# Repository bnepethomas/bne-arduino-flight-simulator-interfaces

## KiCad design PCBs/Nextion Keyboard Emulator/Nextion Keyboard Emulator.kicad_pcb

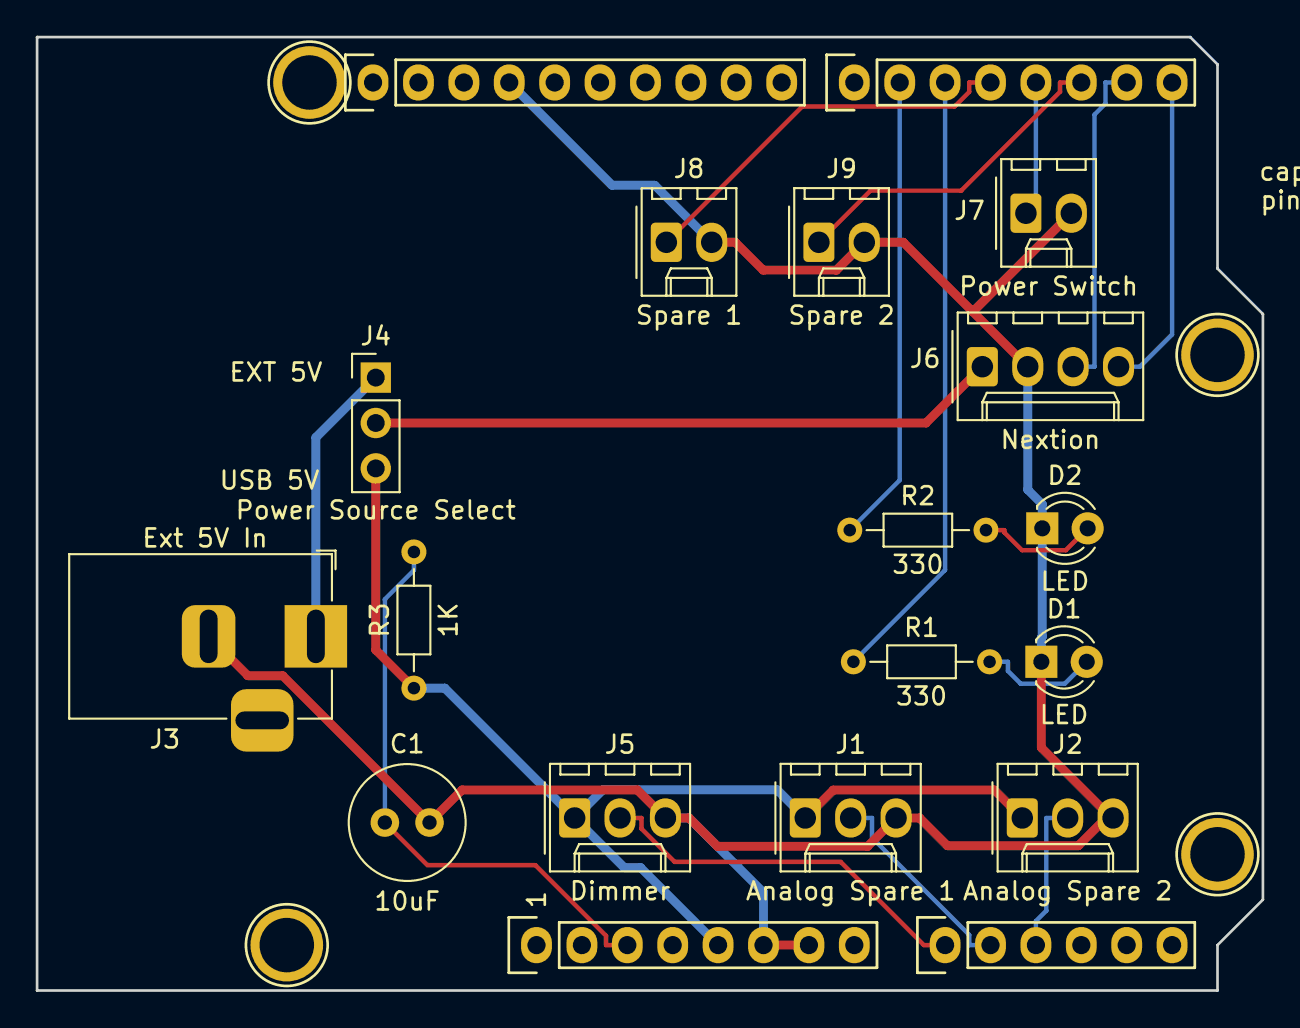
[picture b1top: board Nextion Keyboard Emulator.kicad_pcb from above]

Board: 2 copper layers, 68.6 x 53.3 mm, 23 parts (0 on the bottom side), 17 nets.

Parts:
C1: 10uF; C_Radial_D6.3mm_H5.0mm_P2.50mm
D1, D2: LED; LED_D3.0mm
J1: Analog Spare 1; Molex_KK-254_AE-6410-03A_1x03_P2.54mm_Vertical
J2: Analog Spare 2; Molex_KK-254_AE-6410-03A_1x03_P2.54mm_Vertical
J3: Ext 5V In; BarrelJack_Horizontal
J4: Power Source Select; PinHeader_1x03_P2.54mm_Vertical
J5: Dimmer; Molex_KK-254_AE-6410-03A_1x03_P2.54mm_Vertical
J6: Nextion; Molex_KK-254_AE-6410-04A_1x04_P2.54mm_Vertical
J7: Power Switch; Molex_KK-254_AE-6410-02A_1x02_P2.54mm_Vertical
J8: Spare 1; Molex_KK-254_AE-6410-02A_1x02_P2.54mm_Vertical
J9: Spare 2; Molex_KK-254_AE-6410-02A_1x02_P2.54mm_Vertical
P1: Power; Socket_Strip_Arduino_1x08
P2: Analog; Socket_Strip_Arduino_1x06
P3: Digital; Socket_Strip_Arduino_1x10
P4: Digital; Socket_Strip_Arduino_1x08
P5, P6, P7, P8: CONN_01X01; Arduino_1pin
R1, R2: 330; R_Axial_DIN0204_L3.6mm_D1.6mm_P7.62mm_Horizontal
R3: 1K; R_Axial_DIN0204_L3.6mm_D1.6mm_P7.62mm_Horizontal

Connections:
+5V: J1.1, J2.1, J4.3, J5.1, P1.5, R3.1
+5VD: J4.2, J6.1
/0(Rx): J6.4, P4.8
/1(Tx): J6.3, P4.7
/2: J9.1, P4.6
/3(**): J7.1, P4.5
/4: J8.1, P4.4
/5(**): P4.3, R1.1
/6(**): P4.2, R2.1
/A0: J5.2, P2.1
/A1: J1.2, P2.2
/A2: J2.2, P2.3
/EXT5VIN: J3.1, J4.1
/Reset: C1.1, P1.3, R3.2
GND: C1.2, D1.1, D2.1, J1.3, J2.3, J3.2, J5.3, J6.2, J7.2, J8.2, J9.2, P1.6, P1.7, P3.4
unnamed: D1.2, R1.2
unnamed: D2.2, R2.2

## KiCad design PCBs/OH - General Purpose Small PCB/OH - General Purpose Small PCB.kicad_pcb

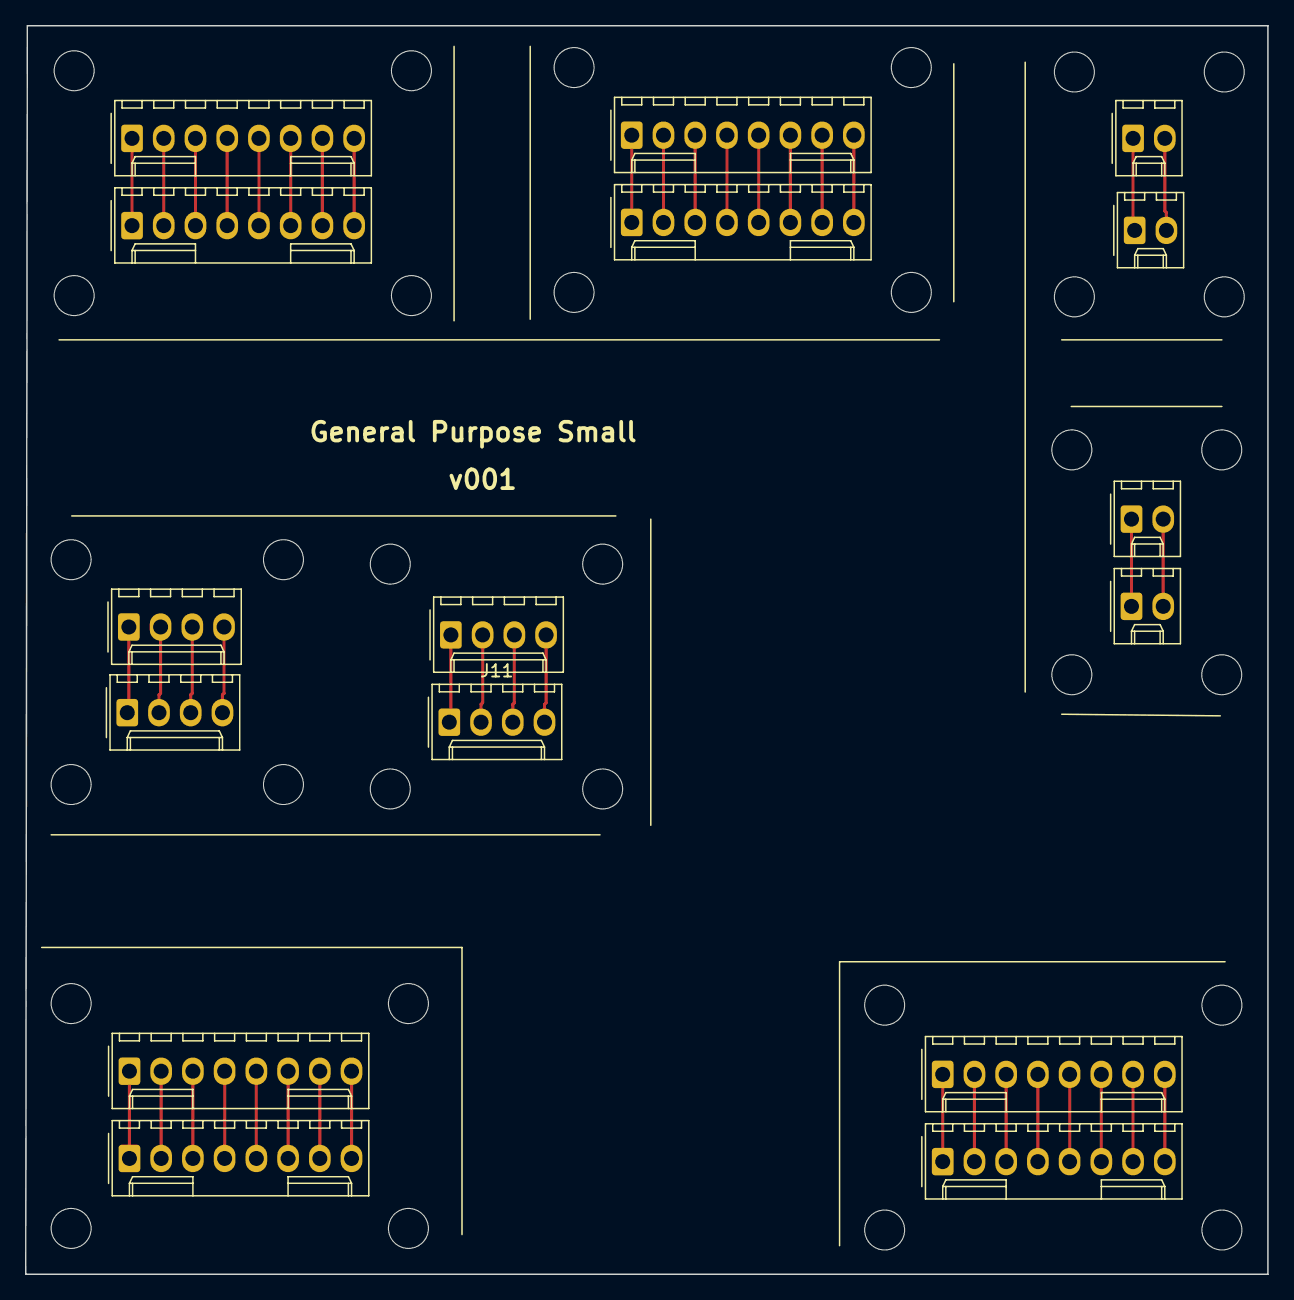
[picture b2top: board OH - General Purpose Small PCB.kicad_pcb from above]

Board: 2 copper layers, 99.4 x 99.9 mm, 48 parts (0 on the bottom side), 44 nets.

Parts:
H1, H2, H3, H4, H5, H6, H7, H8, H9, H10, H11, H12, H13, H14, H15, H16, H17, H18, H19, H20, H21, H22, H23, H24, H25, H26, H27, H28, H29, H30, H31, H32: MountingHole; MountingHole_3.2mm_M3
J1, J2, J3, J4, J5, J6, J7, J8: Conn_01x08_Female; Molex_1x08_P2.54mm_Vertical
J9, J10, J13, J14: Conn_01x02_Female; Molex_1x02_P2.54mm_Vertical
J11, J12, J15, J16: Conn_01x04_Female; Molex_1x04_P2.54mm_Vertical

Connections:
unnamed: J1.1, J5.1
unnamed: J1.2, J5.2
unnamed: J1.3, J5.3
unnamed: J1.4, J5.4
unnamed: J1.5, J5.5
unnamed: J1.6, J5.6
unnamed: J1.7, J5.7
unnamed: J1.8, J5.8
unnamed: J2.1, J6.1
unnamed: J2.2, J6.2
unnamed: J2.3, J6.3
unnamed: J2.4, J6.4
unnamed: J2.5, J6.5
unnamed: J2.6, J6.6
unnamed: J2.7, J6.7
unnamed: J2.8, J6.8
unnamed: J3.1, J7.1
unnamed: J3.2, J7.2
unnamed: J3.3, J7.3
unnamed: J3.4, J7.4
unnamed: J3.5, J7.5
unnamed: J3.6, J7.6
unnamed: J3.7, J7.7
unnamed: J3.8, J7.8
unnamed: J4.1, J8.1
unnamed: J4.2, J8.2
unnamed: J4.3, J8.3
unnamed: J4.4, J8.4
unnamed: J4.5, J8.5
unnamed: J4.6, J8.6
unnamed: J4.7, J8.7
unnamed: J4.8, J8.8
unnamed: J10.1, J14.1
unnamed: J10.2, J14.2
unnamed: J11.1, J15.1
unnamed: J11.2, J15.2
unnamed: J11.3, J15.3
unnamed: J11.4, J15.4
unnamed: J12.1, J16.1
unnamed: J12.2, J16.2
unnamed: J12.3, J16.3
unnamed: J12.4, J16.4
unnamed: J9.1, J13.1
unnamed: J9.2, J13.2

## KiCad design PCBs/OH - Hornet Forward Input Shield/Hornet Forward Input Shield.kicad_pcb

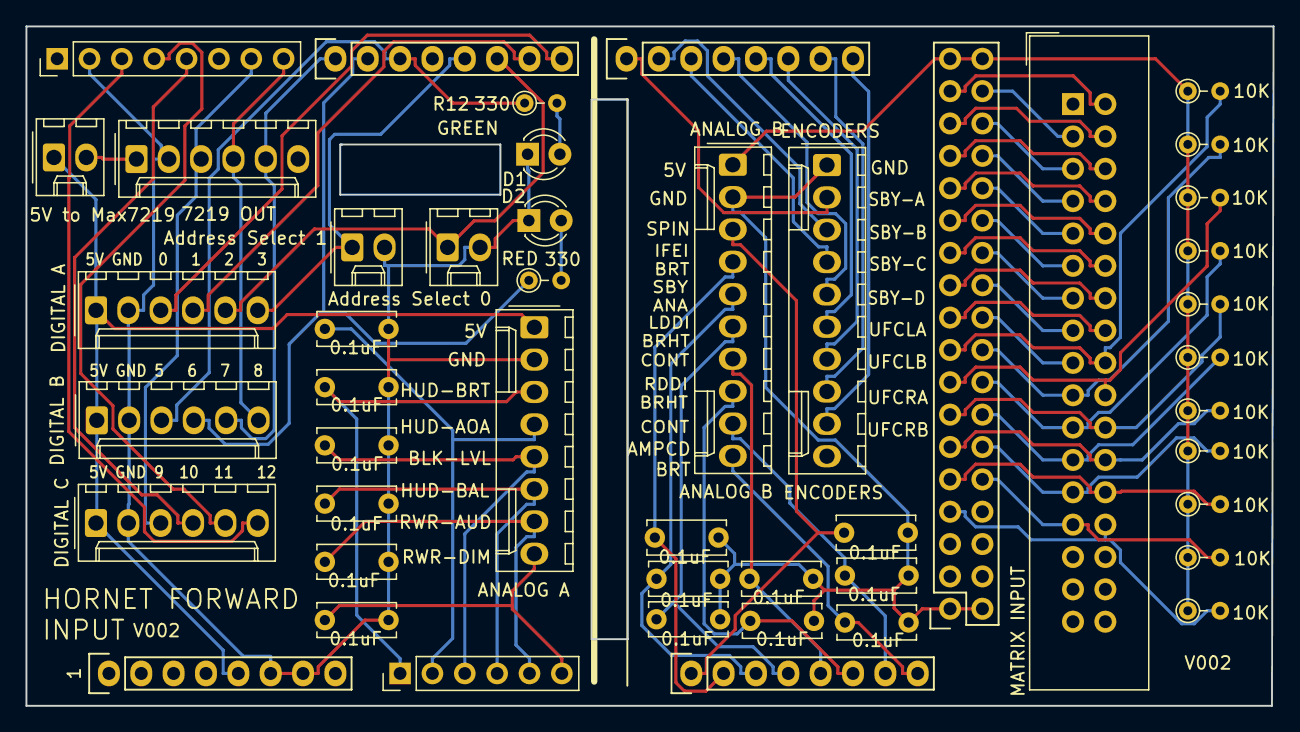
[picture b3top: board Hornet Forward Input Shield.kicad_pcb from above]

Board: 2 copper layers, 97.9 x 53.3 mm, 47 parts (0 on the bottom side), 68 nets.

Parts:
C1, C2, C3, C4, C5, C6, C7, C8, C9, C10, C11, C12, C13, C14: 0.1uF; C_Disc_D6.0mm_W2.5mm_P5.00mm
D1: GREEN; LED_D3.0mm
D2: RED; LED_D3.0mm
J1: MATRIX INPUT; IDC-Header_2x17_P2.54mm_Vertical
J2: 5V to Max7219; Molex_1x02_P2.54mm_Vertical
J3: 7219 OUT; Molex_1x06_P2.54mm_Vertical
J4: ANALOG B; Molex_1x10_P2.54mm_Vertical
J5: ENCODERS; Molex_1x10_P2.54mm_Vertical
J6: ANALOG A; Molex_1x08_P2.54mm_Vertical
J7: Address Select 0; Molex_1x02_P2.54mm_Vertical
J8: Address Select 1; Molex_1x02_P2.54mm_Vertical
J9: DIGITAL A; Molex_1x06_P2.54mm_Vertical
J10: DIGITAL B; Molex_1x06_P2.54mm_Vertical
J11: DIGITAL C; Molex_1x06_P2.54mm_Vertical
P1: Power; Socket_Strip_Arduino_1x08
P2: Analog; PinHeader_1x06_P2.54mm_Vertical
P3: Analog; Socket_Strip_Arduino_1x08
P4: Digital; Socket_Strip_Arduino_2x18
P5: PWM; PinHeader_1x08_P2.54mm_Vertical
P6: PWM; Socket_Strip_Arduino_1x08
P7: Communication; Socket_Strip_Arduino_1x08
R1, R2, R3, R4, R5, R6, R7, R8, R9, R10, R11: 10K; PT_R_Axial_DIN0204_L3.6mm_D1.6mm_P2.54mm_Vertical
R12, R13: 330; PT_R_Axial_DIN0204_L3.6mm_D1.6mm_P2.54mm_Vertical

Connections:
+5V: J4.1, P4.35, P4.36, R1.1, R2.1, R3.1, R4.1, R5.1, R6.1, R7.1, R8.1, R9.1, R10.1, R11.1
+5VL: J2.1, J6.1, J9.1, J10.1, J11.1, P1.5
/14(Tx3): J5.2, P7.1
/15(Rx3): J5.3, P7.2
/16(Tx2): J5.4, P7.3
/17(Rx2): J5.5, P7.4
/18(Tx1): J5.6, P7.5
/19(Rx1): J5.7, P7.6
/20(SDA): J5.8, P7.7
/21(SCL): J5.9, P7.8
/22: J1.2, P4.33
/23: J1.3, P4.34
/24: J1.4, P4.31
/25: J1.5, P4.32
/26: J1.6, P4.29
/27: J1.7, P4.30
/28: J1.8, P4.27
/29: J1.9, P4.28
/30: J1.10, P4.25
/31: J1.11, P4.26
/32: J1.12, P4.23
/33: J1.13, P4.24
/34: J1.14, P4.21
/35: J1.15, P4.22
/36: J1.16, P4.19
/37: J1.17, P4.20
/38: J1.18, P4.17, R1.2
/39: J1.19, P4.18, R2.2
/40: J1.20, P4.15, R3.2
/41: J1.21, P4.16, R4.2
/42: J1.22, P4.13, R5.2
/43: J1.23, P4.14, R6.2
/44: J1.24, P4.11, R7.2
/45: J1.25, P4.12, R8.2
/46: J1.26, P4.9, R9.2
/47: J1.27, P4.10, R10.2
/48: J1.28, P4.7, R11.2
/A0: C11.1, J6.3, P2.1
/A1: C9.1, J6.4, P2.2
/A2: C7.1, J6.5, P2.3
/A3: C5.1, J6.6, P2.4
/A4: C3.1, J6.7, P2.5
/A5: C1.1, J6.8, P2.6
/A8: C14.1, J4.3, P3.1
/A9: C13.1, J4.4, P3.2
/A10: C12.1, J4.5, P3.3
/A11: C10.1, J4.6, P3.4
/A12: C8.1, J4.7, P3.5
/A13: C6.1, J4.8, P3.6
/A14: C4.1, J4.9, P3.7
/A15: C2.1, J4.10, P3.8
/D0: J9.3, P6.8
/D1: J9.4, P6.7
/D2: J7.1, J9.5, P6.6
/D3: J8.1, J9.6, P6.5
/D5: J10.3, P6.3, R12.1
/D6: J10.4, P6.2, R13.1
/D7: J3.5, J10.5, P6.1
/D8: J3.4, J10.6, P5.8
/D9: J3.3, J11.3, P5.7
/D11: J11.4, P5.5
/D12: J11.5, P5.4
/D13: J11.6, P5.3
GND: C2.2, C4.2, C6.2, C8.2, C10.2, C12.2, C13.2, C14.2, J4.2, J5.1, P4.1, P4.2
GNDD: C1.2, C3.2, C5.2, C7.2, C9.2, C11.2, D1.1, D2.1, J3.2, J6.2, J7.2, J8.2, J9.2, J10.2, J11.2, P1.6, P1.7, P5.2
unnamed: D1.2, R12.2
unnamed: D2.2, R13.2
unnamed: J2.2, J3.1

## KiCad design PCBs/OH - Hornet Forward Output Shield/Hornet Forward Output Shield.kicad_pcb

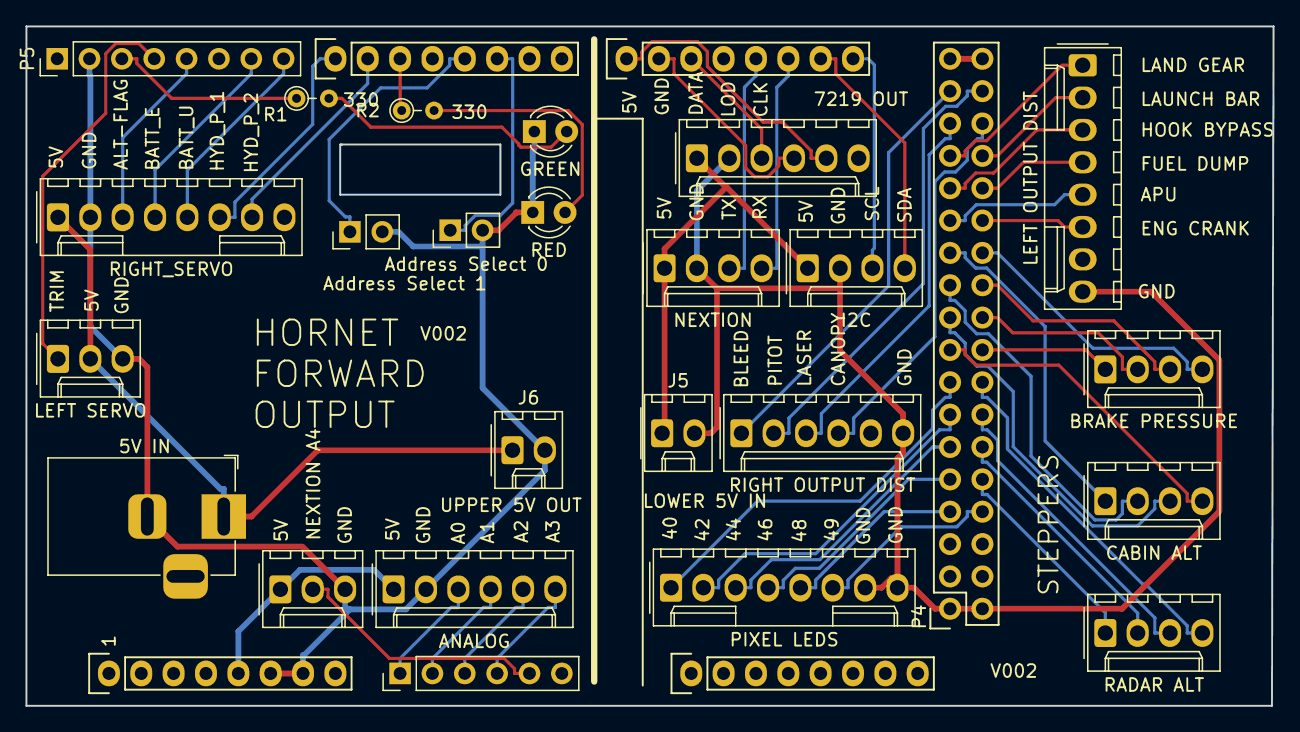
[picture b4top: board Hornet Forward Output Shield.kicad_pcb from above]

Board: 2 copper layers, 97.9 x 53.3 mm, 29 parts (0 on the bottom side), 58 nets.

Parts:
D1: GREEN; LED_D3.0mm
D2: RED; LED_D3.0mm
J1: LEFT OUTPUT DIST; Molex_1x08_P2.54mm_Vertical
J2: RIGHT OUTPUT DIST; Molex_1x06_P2.54mm_Vertical
J3: LEFT SERVO; Molex_1x03_P2.54mm_Vertical
J4: RIGHT_SERVO; Molex_1x08_P2.54mm_Vertical
J5: LOWER 5V IN; Molex_1x02_P2.54mm_Vertical
J6: UPPER 5V OUT; Molex_1x02_P2.54mm_Vertical
J7: NEXTION; Molex_1x04_P2.54mm_Vertical
J8: 7219 OUT; Molex_1x06_P2.54mm_Vertical
J9: PIXEL LEDS; Molex_1x08_P2.54mm_Vertical
J10: I2C; Molex_1x04_P2.54mm_Vertical
J11: 5V IN; BarrelJack_Horizontal
J12: CABIN ALT; Molex_1x04_P2.54mm_Vertical
J13: BRAKE PRESSURE; Molex_1x04_P2.54mm_Vertical
J14: RADAR ALT; Molex_1x04_P2.54mm_Vertical
J15: ANALOG; Molex_1x06_P2.54mm_Vertical
J16: Address Select 0; PinHeader_1x02_P2.54mm_Vertical
J17: Address Select 1; PinHeader_1x02_P2.54mm_Vertical
J18: NEXTION ANA; Molex_1x03_P2.54mm_Vertical
P1: Power; Socket_Strip_Arduino_1x08
P2: Analog; PinHeader_1x06_P2.54mm_Vertical
P3: Analog; Socket_Strip_Arduino_1x08
P4: Digital; Socket_Strip_Arduino_2x18
P5: PWM; PinHeader_1x08_P2.54mm_Vertical
P6: PWM; Socket_Strip_Arduino_1x08
P7: Communication; Socket_Strip_Arduino_1x08
R1, R2: 330; PT_R_Axial_DIN0204_L3.6mm_D1.6mm_P2.54mm_Vertical

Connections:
+5V: P4.35, P4.36
+5VL: J15.1, J18.1, P1.5
/14(Tx3): J8.5, P7.1
/15(Rx3): J8.4, P7.2
/16(Tx2): J8.3, P7.3
/18(Tx1): J7.3, P7.5
/19(Rx1): J7.4, P7.6
/20(SDA): J10.4, P7.7
/21(SCL): J10.3, P7.8
/22: J2.1, P4.33
/23: J2.2, P4.34
/24: J2.3, P4.31
/25: J2.4, P4.32
/26: J1.1, P4.29
/27: J1.2, P4.30
/28: J1.3, P4.27
/29: J1.4, P4.28
/30: J1.5, P4.25
/31: J1.6, P4.26
/32: J12.1, P4.23
/33: J13.4, P4.24
/34: J12.2, P4.21
/35: J13.3, P4.22
/36: J12.3, P4.19
/37: J13.2, P4.20
/38: J12.4, P4.17
/39: J13.1, P4.18
/40: J9.1, P4.15
/41: J14.4, P4.16
/42: J9.2, P4.13
/43: J14.3, P4.14
/44: J9.3, P4.11
/45: J14.2, P4.12
/46: J9.4, P4.9
/47: J14.1, P4.10
/48: J9.5, P4.7
/49: J9.6, P4.8
/A0: J15.3, P2.1
/A1: J15.4, P2.2
/A2: J15.5, P2.3
/A3: J15.6, P2.4
/A4: J18.2, P2.5
/ADDRESS_SELECT_0: J16.1, P6.6
/ADDRESS_SELECT_1: J17.1, P6.5
/D5: P6.3, R2.1
/D6: J4.7, P6.2
/D7: J4.6, P6.1
/D8: J4.5, P5.8
/D9: J4.4, P5.7
/D11: J4.3, P5.5
/D12: J3.1, P5.4
/D13: P5.3, R1.1
/LOWER_OUTPUT_5V: J5.1, J7.1, J8.1, J10.1
/UPPER_OUTPUT_5V: J3.2, J4.1, J6.1, J11.1
GND: J1.8, J2.6, J5.2, J7.2, J8.2, J9.7, J9.8, J10.2, P4.1, P4.2
GNDD: D1.1, D2.1, J3.3, J4.2, J6.2, J11.2, J15.2, J16.2, J17.2, J18.3, P1.6, P1.7, P5.2
unnamed: D1.2, R1.2
unnamed: D2.2, R2.2

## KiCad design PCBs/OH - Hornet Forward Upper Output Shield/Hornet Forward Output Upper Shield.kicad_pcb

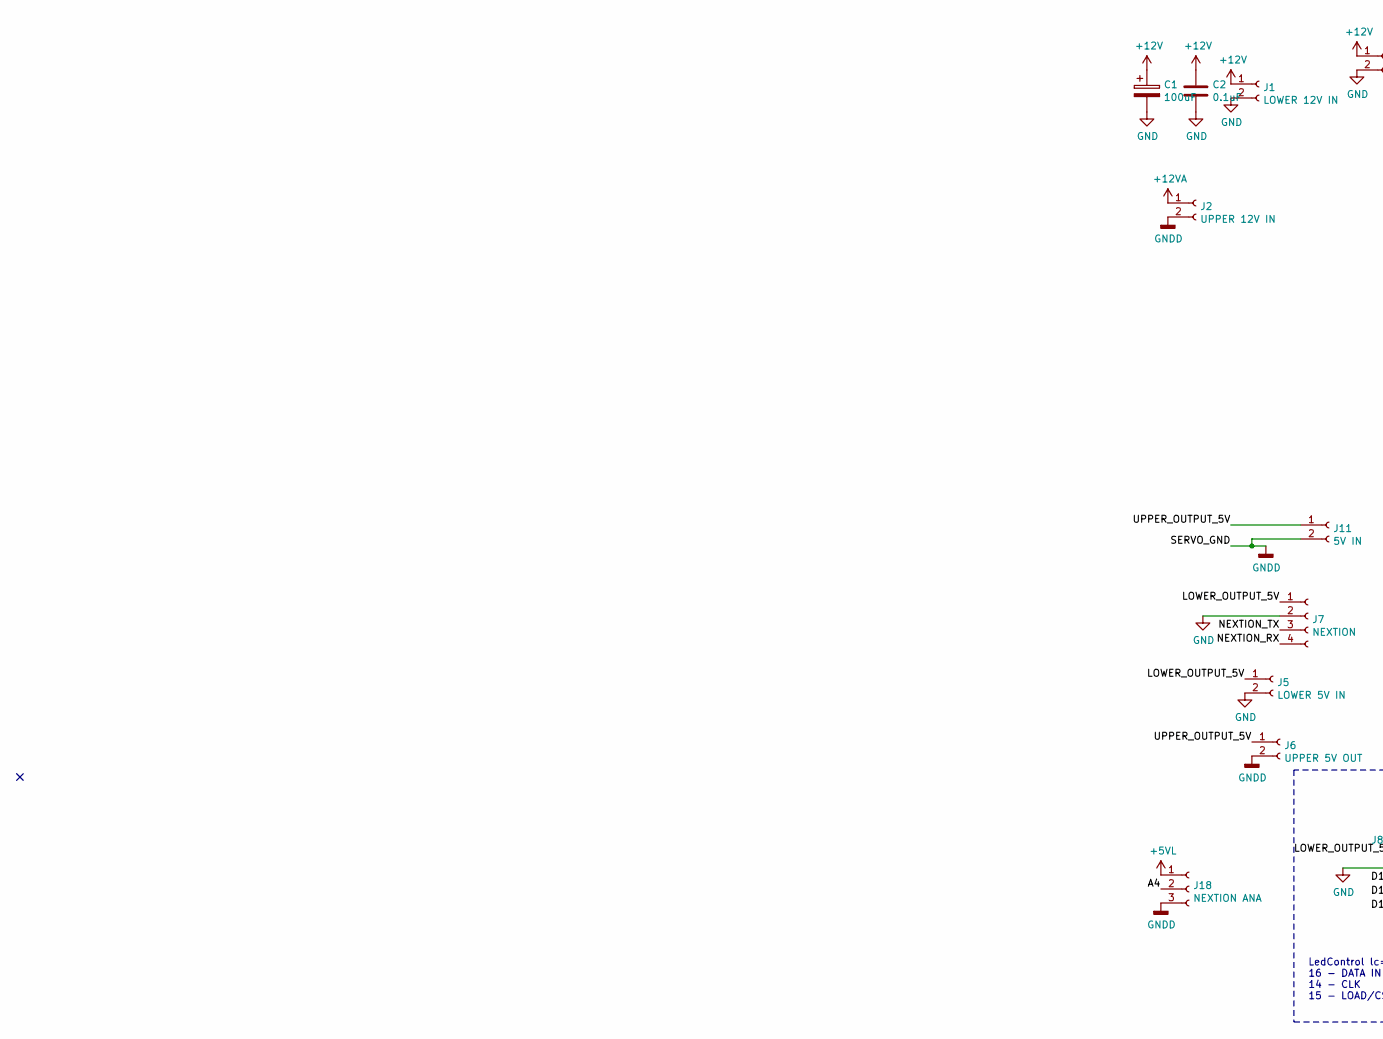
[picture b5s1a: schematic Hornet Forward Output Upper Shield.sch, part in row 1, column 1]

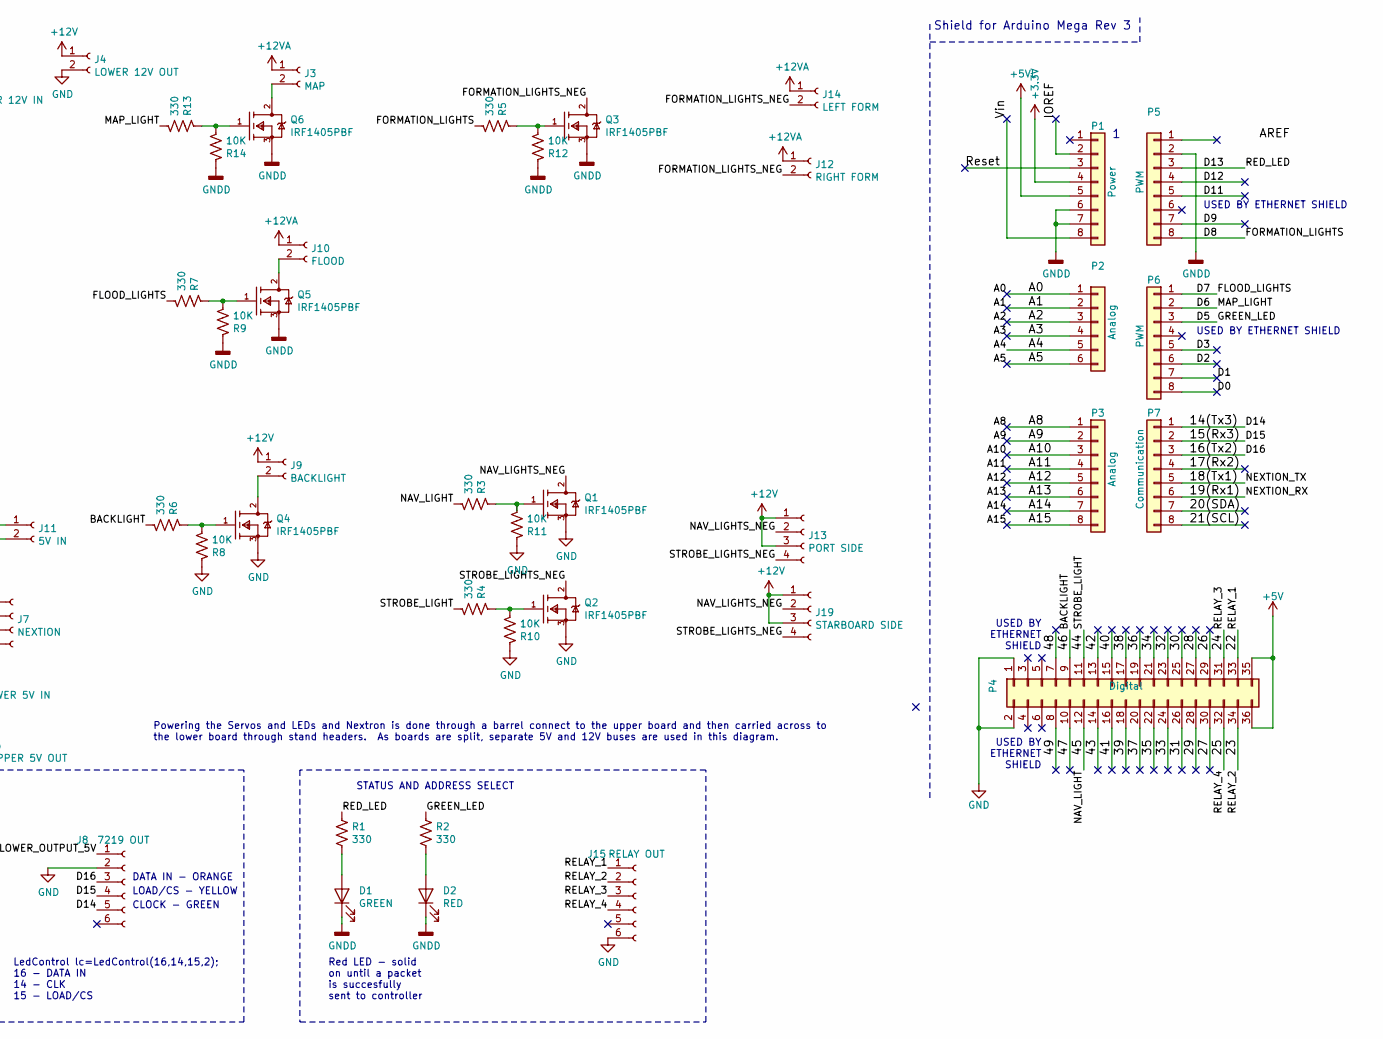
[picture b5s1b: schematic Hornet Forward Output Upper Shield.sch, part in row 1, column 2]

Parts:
C1: 100uF; CP_Radial_D5.0mm_P2.50mm
C2: 0.1uF; C_Disc_D4.3mm_W1.9mm_P5.00mm
D1: GREEN; LED_D3.0mm
D2: RED; LED_D3.0mm
J1: LOWER 12V IN; Molex_1x02_P2.54mm_Vertical
J2: UPPER 12V IN; Molex_1x02_P2.54mm_Vertical
J3: MAP; Molex_1x02_P2.54mm_Vertical
J4: LOWER 12V OUT; Molex_1x02_P2.54mm_Vertical
J5: LOWER 5V IN; Molex_1x02_P2.54mm_Vertical
J6: UPPER 5V OUT; Molex_1x02_P2.54mm_Vertical
J7: NEXTION; Molex_1x04_P2.54mm_Vertical
J8: 7219 OUT; Molex_1x06_P2.54mm_Vertical
J9: BACKLIGHT; Molex_1x02_P2.54mm_Vertical
J10: FLOOD; Molex_1x02_P2.54mm_Vertical
J11: 5V IN; BarrelJack_Horizontal
J12: RIGHT FORM; Molex_1x02_P2.54mm_Vertical
J13: PORT SIDE; Molex_1x04_P2.54mm_Vertical
J14: LEFT FORM; Molex_1x02_P2.54mm_Vertical
J15: RELAY OUT; Molex_1x06_P2.54mm_Vertical
J18: NEXTION ANA; Molex_1x03_P2.54mm_Vertical
J19: STARBOARD SIDE; Molex_1x04_P2.54mm_Vertical
P1: Power; Socket_Strip_Arduino_1x08
P2: Analog; PinHeader_1x06_P2.54mm_Vertical
P3: Analog; Socket_Strip_Arduino_1x08
P4: Digital; Socket_Strip_Arduino_2x18
P5: PWM; PinHeader_1x08_P2.54mm_Vertical
P6: PWM; Socket_Strip_Arduino_1x08
P7: Communication; Socket_Strip_Arduino_1x08
Q1, Q2, Q3, Q4, Q5, Q6: IRF1405PBF; TO-220-3_Vertical; mouser part number 942-IRF1405PBF; digikey description MOSFET N-CH 55V 169A TO-220AB
R1, R2, R3, R4, R5, R6, R7, R13: 330; PT_R_Axial_DIN0204_L3.6mm_D1.6mm_P2.54mm_Vertical
R8, R9, R10, R11, R12, R14: 10K; PT_R_Axial_DIN0204_L3.6mm_D1.6mm_P2.54mm_Vertical

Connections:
+3V3: P1.4
+5V: P4.35, P4.36
+5VL: J18.1, P1.5
+12V: C1.1, C2.1, J1.1, J4.1, J9.1, J13.1, J13.3, J19.1, J19.3
+12VA: J2.1, J3.1, J10.1, J12.1, J14.1
/14(Tx3): J8.5, P7.1
/15(Rx3): J8.4, P7.2
/16(Tx2): J8.3, P7.3
/17(Rx2): P7.4
/18(Tx1): J7.3, P7.5
/19(Rx1): J7.4, P7.6
/20(SDA): P7.7
/21(SCL): P7.8
/22: J15.1, P4.33
/23: J15.2, P4.34
/24: J15.3, P4.31
/25: J15.4, P4.32
/26: P4.29
/27: P4.30
/28: P4.27
/29: P4.28
/30: P4.25
/31: P4.26
/32: P4.23
/33: P4.24
/34: P4.21
/35: P4.22
/36: P4.19
/37: P4.20
/38: P4.17
/39: P4.18
/40: P4.15
/41: P4.16
/42: P4.13
/43: P4.14
/44: P4.11, R4.2
/45: P4.12, R3.2
/46: P4.9, R6.2
/47: P4.10
/48: P4.7
/49: P4.8
/A0: P2.1
/A1: P2.2
/A2: P2.3
/A3: P2.4
/A4: J18.2, P2.5
/A5: P2.6
/A8: P3.1
/A9: P3.2
/A10: P3.3
/A11: P3.4
/A12: P3.5
/A13: P3.6
/A14: P3.7
/A15: P3.8
/Compass_Stepper_A: P5.4; also elsewhere on the board
/Compass_Stepper_B: P5.5; also elsewhere on the board
/Compass_Stepper_C: P6.5; also elsewhere on the board
/Compass_Stepper_D: P6.6; also elsewhere on the board
/Compass_Zero_Sensor: P5.7; also elsewhere on the board
/D0: P6.8
/D1: P6.7
/D5: P6.3, R2.1
/D6: P6.2, R13.2
/D7: P6.1, R7.2
/D8: P5.8, R5.2
/D13: P5.3, R1.1
/FORMATION_LIGHTS_NEG: J12.2, J14.2, Q3.2 (D)
/IOREF: P1.2
/LOWER_OUTPUT_5V: J5.1, J7.1, J8.1
/NAV_LIGHTS_NEG: J13.2, J19.2, Q1.2 (D)
/Reset: P1.3
/STROBE_LIGHTS_NEG: J13.4, J19.4, Q2.2 (D)
/UPPER_OUTPUT_5V: J6.1, J11.1; also elsewhere on the board
/Vin: P1.8
GND: C1.2, C2.2, J1.2, J4.2, J5.2, J7.2, J8.2, J15.6, P4.1, P4.2, Q1.3 (S), Q2.3 (S), Q4.3 (S), R8.1, R10.1, R11.1
GNDD: D1.1 (K), D2.1 (K), J2.2, J6.2, J11.2, J18.3, P1.6, P1.7, P5.2, Q3.3 (S), Q5.3 (S), Q6.3 (S), R9.1, R12.1, R14.1; also elsewhere on the board
unnamed: D1.2 (A), R1.2
unnamed: D2.2 (A), R2.2
unnamed: J3.2, Q6.2 (D)
unnamed: J9.2, Q4.2 (D)
unnamed: J10.2, Q5.2 (D)
unnamed: Q1.1 (G), R3.1, R11.2
unnamed: Q2.1 (G), R4.1, R10.2
unnamed: Q3.1 (G), R5.1, R12.2
unnamed: Q4.1 (G), R6.1, R8.2
unnamed: Q5.1 (G), R7.1, R9.2
unnamed: Q6.1 (G), R13.1, R14.2

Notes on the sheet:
Shield for Arduino Mega Rev 3
USED BY ETHERNET SHIELD
USED BY ETHERNET SHIELD
Red LED - solid on until a packet is succesfully sent to controller
DATA IN - ORANGE
LOAD/CS - YELLOW
CLOCK - GREEN
LedControl lc=LedControl(16,14,15,2); 16 - DATA IN 14 - CLK 15 - LOAD/CS
STATUS AND ADDRESS SELECT
Powering the Servos and LEDs and Nextron is done through a barrel connect to the upper board and then carried across to the lower board through stand headers. As boards are split, separate 5V and 12V buses are used in this diagram.

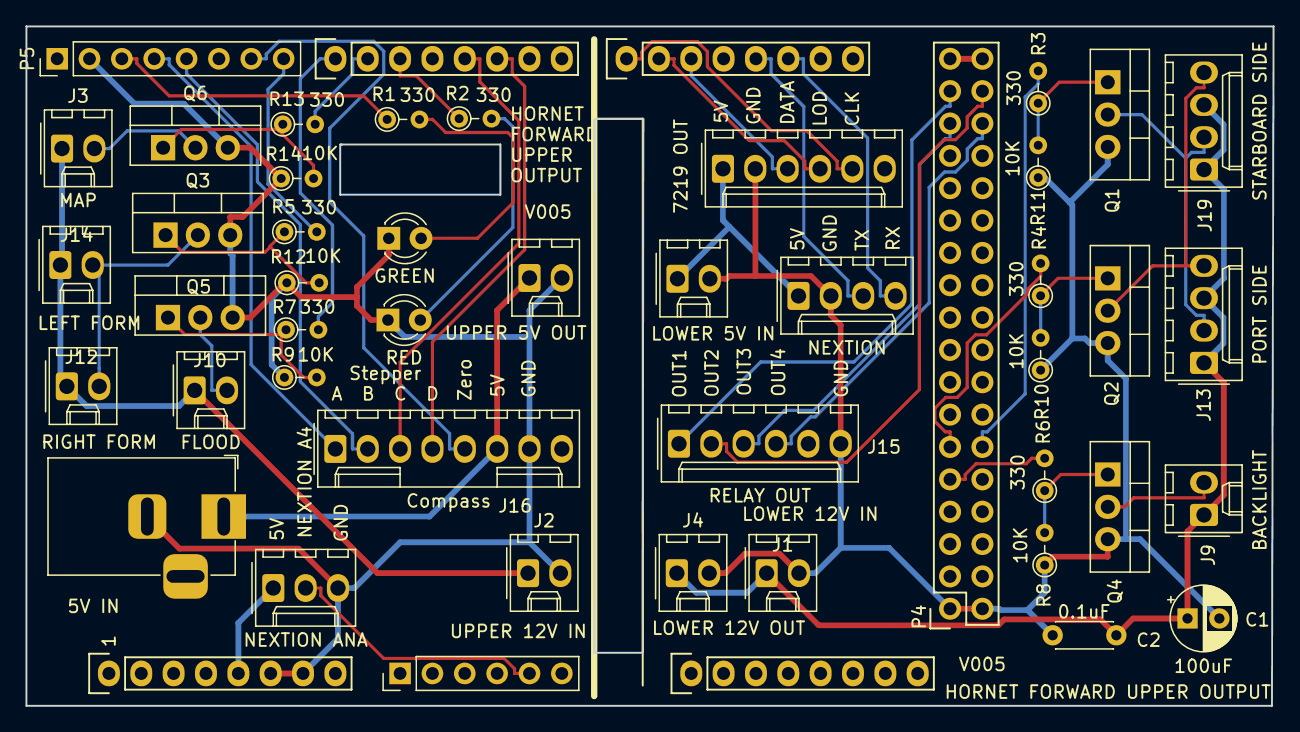
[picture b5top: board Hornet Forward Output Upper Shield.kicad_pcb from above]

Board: 2 copper layers, 97.9 x 53.3 mm, 49 parts (0 on the bottom side), 45 nets.

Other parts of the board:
J16: Compass; Molex_1x08_P2.54mm_Vertical

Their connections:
/Compass_Stepper_A: J16.1; also elsewhere on the board
/Compass_Stepper_B: J16.2; also elsewhere on the board
/Compass_Stepper_C: J16.3; also elsewhere on the board
/Compass_Stepper_D: J16.4; also elsewhere on the board
/Compass_Zero_Sensor: J16.5; also elsewhere on the board
/UPPER_OUTPUT_5V: J16.6; also elsewhere on the board
GNDD: J16.7; also elsewhere on the board

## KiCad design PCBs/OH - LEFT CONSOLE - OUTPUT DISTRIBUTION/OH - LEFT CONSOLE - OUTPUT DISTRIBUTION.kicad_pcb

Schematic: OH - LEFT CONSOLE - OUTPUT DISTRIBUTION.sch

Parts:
H1, H2, H3, H4: MountingHole; MountingHole_3.2mm_M3
J1: CENTRAL OUTPUT; Molex_1x08_P2.54mm_Vertical
J2: LED IN; Molex_1x03_P2.54mm_Vertical
J3: Power In; Molex_1x02_P2.54mm_Vertical
J4: Brake Pressure In; Molex_1x04_P2.54mm_Vertical
J5: APU LED; Molex_1x02_P2.54mm_Vertical
J6: LANDING GEAR LED; Molex_1x02_P2.54mm_Vertical
J7: Landing Gear Sol; Molex_1x02_P2.54mm_Vertical
J8: Select Jet; Molex_1x04_P2.54mm_Vertical
J9: Fuel Dump; Molex_1x02_P2.54mm_Vertical
J10: Brake Pressure Out; Molex_1x04_P2.54mm_Vertical
J11: APU; Molex_1x04_P2.54mm_Vertical
J12: Trim Servo In; Molex_1x03_P2.54mm_Vertical
J13: Trim Servo Out; Molex_1x03_P2.54mm_Vertical
U1: ULN2003A; DIP-16_W7.62mm

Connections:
/+12V: J3.1, J7.1, J8.1, J8.3, J9.1, J11.1, J11.3, U1.9 (COM)
/GND: J1.8, J3.2, U1.7 (I7), U1.8 (GND)
/In_APU_Mag: J1.5, U1.5 (I5)
/In_Engine_Crank_Mag: J1.6, U1.6 (I6)
/In_Fuel_Dump_Mag: J1.4, U1.4 (I4)
/In_Hook_Bypass_Mag: J1.3, U1.3 (I3)
/In_Landing_Gear_Sol: J1.1, U1.1 (I1)
/In_Launch_Bar_Mag: J1.2, U1.2 (I2)
/LEDCOL1: J2.3, J5.2, J6.2
/LEDROW1: J2.1, J5.1
/LEDROW2: J2.2, J6.1
/Out_APU_Mag: J11.2, U1.12 (O5)
/Out_Engine_Crank_Mag: J11.4, U1.11 (O6)
/Out_Fuel_Dump_Mag: J9.2, U1.13 (O4)
/Out_Hook_Bypass_Mag: J8.4, U1.14 (O3)
/Out_Landing_Gear_Sol: J7.2, U1.16 (O1)
/Out_Launch_Bar_Mag: J8.2, U1.15 (O2)
/SERVO_5V: J12.2, J13.2
/SERVO_GND: J12.3, J13.3
/SERVO_PWM: J12.1, J13.1
unnamed: J4.1, J10.1
unnamed: J4.2, J10.2
unnamed: J4.3, J10.3
unnamed: J4.4, J10.4

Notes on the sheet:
Left Console APU - LED - Include Resistor Landing Gear Handle - LED - Include Resistor Landing Gear - Solenoid Launch Bar - Mag Switch Hook Bypass - Mag Switch APU - Mag Switch Engine Crank - Mag Switch Fuel Dump - Mag Switch Trim - Servo Brake Pressure - Stepper

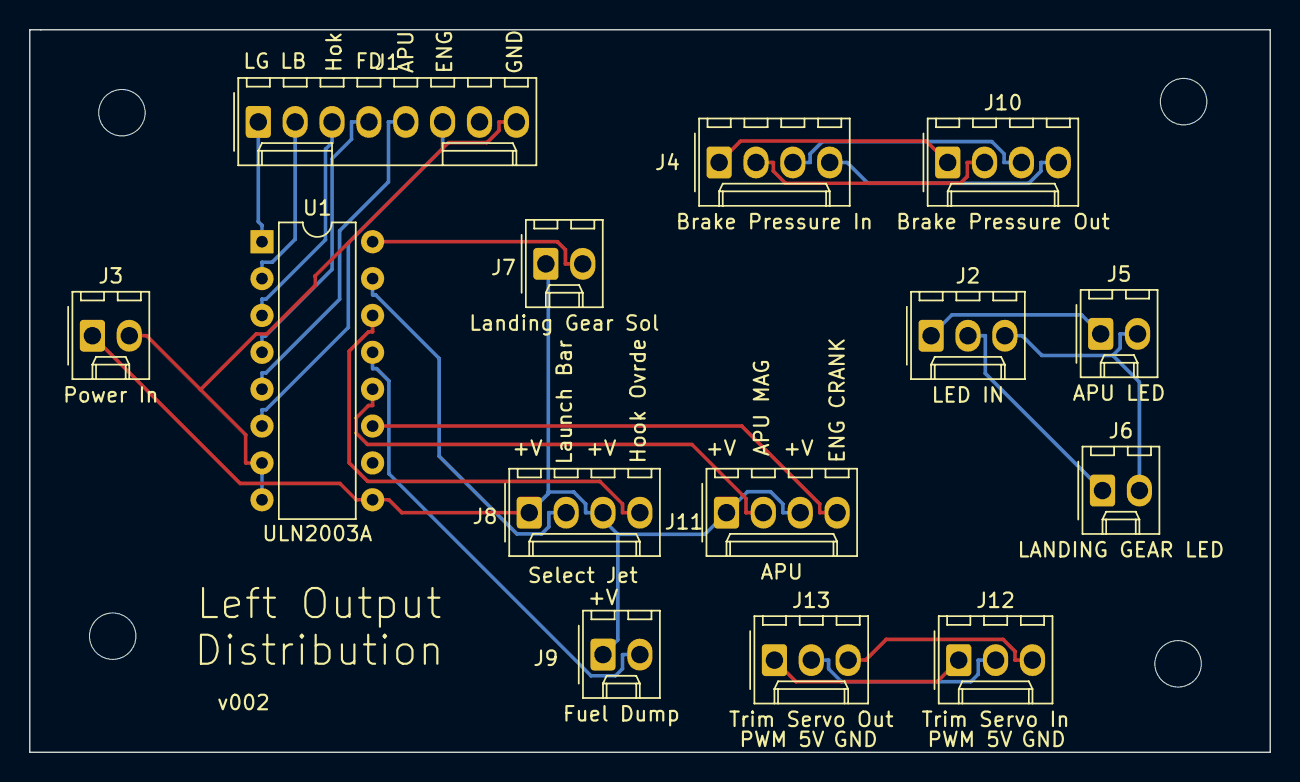
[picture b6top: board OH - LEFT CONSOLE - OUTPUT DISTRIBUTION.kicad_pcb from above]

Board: 2 copper layers, 85.5 x 49.8 mm, 18 parts (0 on the bottom side), 24 nets.
